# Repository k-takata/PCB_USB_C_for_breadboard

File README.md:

# ブレッドボード用 USB Type-C 電源アダプター (Rev. 4)

## 概要

USB Type-Cからブレッドボードに電源を供給するためのアダプターです。
供給電圧は5Vと3.3Vをジャンパーピンで選択できます。

## 使用したソフトウェア

KiCad 9.0

## 回路図

## 基板パターン図

## 部品表

| Reference           |個数|値    | 説明 |
|---------------------|----|------|------|
|C1                   |   1| 10μF|積層セラミックコンデンサー 3225M|
|D1                   |   1|      |角形LED (あるいは3mm LEDや1608MチップLED)|
|F1 (\*1)             |   1|  1.1A|[ポリヒューズ](https://akizukidenshi.com/catalog/g/g100507/)|
|F2 (\*1)             |   1|  0.5A|[ポリヒューズ](https://akizukidenshi.com/catalog/g/g115300/)、表面実装|
|J1                   |   1|      |[USB Type-Cコネクター](https://akizukidenshi.com/catalog/g/g114356/)|
|J2, J3               |   2|      |細ピンヘッダー 1x2、ブレッドボードへの挿入用、裏面に取り付け|
|J4                   |   1|      |ピンヘッダー 1x3、出力電圧設定用|
|J5                   |   1|      |ピンソケット 1x5|
|R1, R2               |   2|5.1kΩ|1608M|
|R3                   |   1|  1kΩ|1/6Wまたは1/4W、LED電流制限用。値はLEDや好みの明るさに応じて適宜調整 (1kΩ~47kΩ)|
|SW1                  |   1|      |[スライドスイッチ](https://akizukidenshi.com/catalog/g/g115707/)|
|U1 (\*2)             |   1|[LM1117GS-3.3](https://akizukidenshi.com/catalog/g/g116989/)|三端子レギュレーター 3.3V 1A|

注:
* (\*1) F1, F2は使用する電流量や実装後のサイズを考慮してどちらかを選択します。基板上にはF1の表示のみあります。
* (\*2) Rev. 2までは[NJM2845DL1-33](https://akizukidenshi.com/catalog/g/g111299/)でした。

## 作成

以下の順で取り付けるのがお勧めです。

* USBコネクター
* 表面のチップ抵抗: R1, R2, (F2, D1)
* 裏面のチップ部品: U1, C1
* 表面右側の部品: J4, R3, D1
* 裏面のピンヘッダー: J2, J3
* 表面下側のピンソケット: J5
* 表面左側の部品: SW1, F1

J5とSW1は少し干渉するので、J5を少し削る必要があるかもしれません。

## 使用方法

基板裏面に取り付けたピンヘッダーJ2, J3をブレッドボードの電源ラインに挿入して使用します。J2, J3に供給する電圧はJ4にジャンパーピンを挿すことで5Vあるいは3.3Vから選択します。
J2, J3の端子は、USBコネクター側がプラス (シルクには`VDD`あるいは`+`の表示)、反対側がマイナス (シルクには`GND`あるいは`-`の表示)です。向きに注意してください。

SW1が電源スイッチです。電源がオンになっていれば、LEDが点灯します。

5Vと3.3Vの両方を使用したい場合や、D+/D-のデータ線を使用したい場合は、J5にコードを接続して使います。

## 変更差分

### Rev. 3とRev. 4の差分

* 基板の幅を約100mil狭くしました。それに合わせていくつかの部品の位置や向きを変更しています。
* ぐらつきが少なくなるよう、J2,J3のドリル径を0.8mmから0.7mmに変更しています。
* ぐらつきが少なくなるよう、J4のドリル径を0.9mmから0.8mmに変更しています。
* SW1を少し外側にずらしてJ5との干渉を減らしています。

### Rev. 2とRev. 3の差分

* U1を[NJM2845DL1-33](https://akizukidenshi.com/catalog/g/g111299/)から、より安価で薄くて小さい[LM1117GS-3.3](https://akizukidenshi.com/catalog/g/g116989/)に変更しています。これにより、ブレッドボードに挿したときにレギュレーターがブレッドボードに当たらなくなりました。
* D1に角形以外のLEDを取り付けた時に干渉しにくいように、R3の向きを逆に変更しています。
* 基板の厚さの設定を1.2mmに変更しています。

### Rev. 1とRev. 2の差分

* Rev. 1では基板の端ギリギリにシルクを配置していたために、シルクが削れてしまっていました。Rev. 2では基板サイズを少し大きくしてわずかに余裕を持たせてあります。
* Rev. 1ではJ5とSW1が干渉していましたが、Rev. 2ではSW1を少し外側にずらして干渉を減らしています。
* Rev. 2では表面実装のポリヒューズを使えるようにしています。
* Rev. 1では基板の厚さ1.6mmで発注していましたが、Rev. 2では1.2mmで発注しています。(KiCadの設定は1.6mmのまま)

## 完成品

Rev. 1

左から順にRev. 1, Rev. 2, Rev. 3

Rev. 1, Rev. 2, Rev. 3の裏面

左から順にRev. 1, Rev. 2, Rev. 3, Rev. 4

ブレッドボードに挿して使用している例 ([ESP32-C3-WROOM-02 Breakout Board](https://github.com/k-takata/PCB_esp32c3_breakout)とともに)

## License

CC0

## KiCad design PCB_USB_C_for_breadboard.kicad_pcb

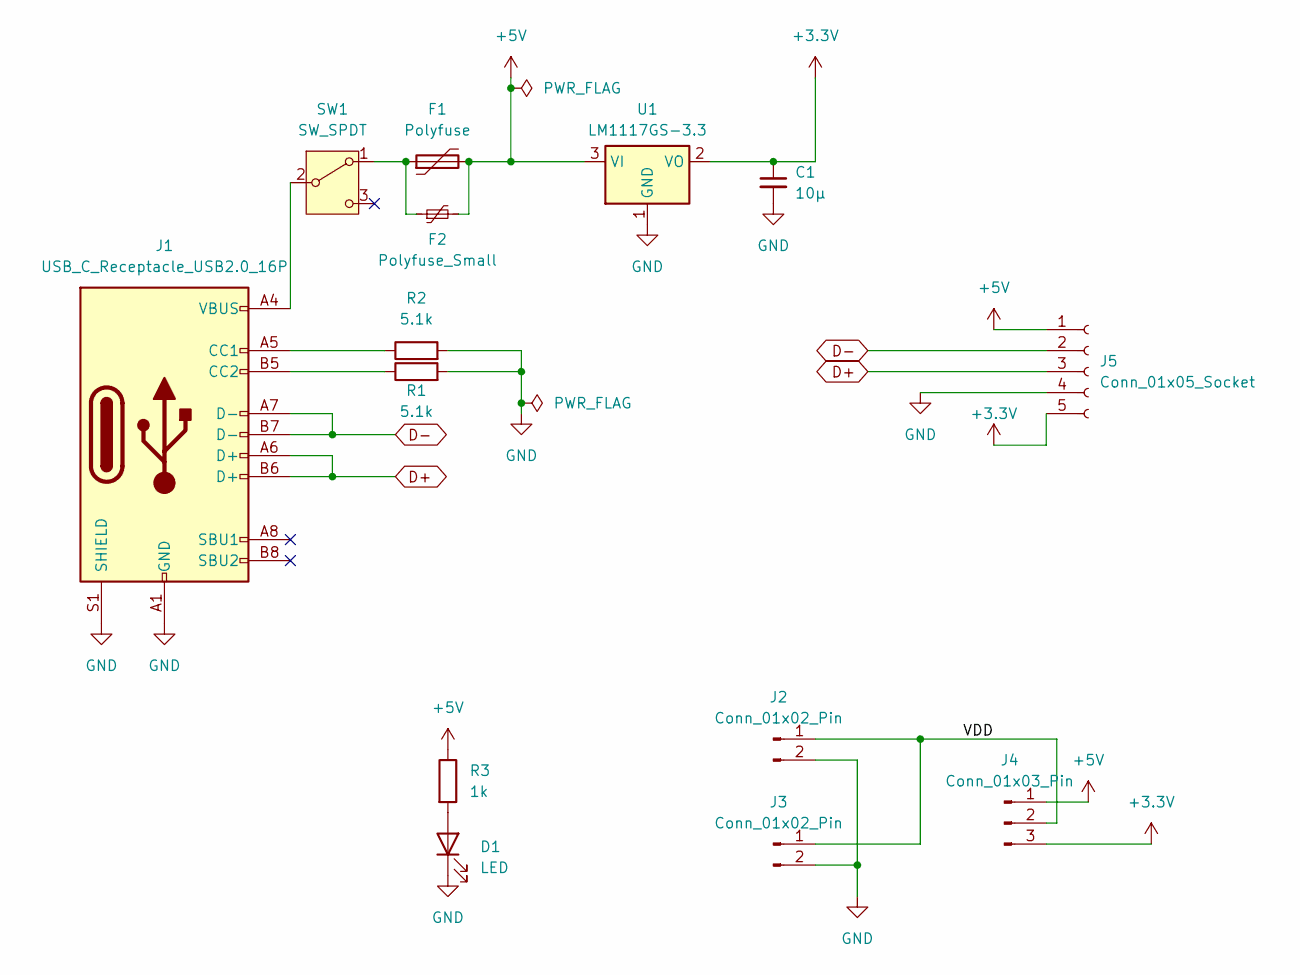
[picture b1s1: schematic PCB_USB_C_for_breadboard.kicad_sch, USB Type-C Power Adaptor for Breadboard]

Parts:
C1: 10μ; C_1210_3225Metric_Pad1.33x2.70mm_HandSolder
D1: LED; LED_Rectangular_W5.0mm_H2.0mm
F1: Polyfuse; C_Disc_D4.3mm_W1.9mm_P5.00mm
F2: Polyfuse_Small; Fuse_1206_3216Metric_Pad1.42x1.75mm_HandSolder
J1: USB_C_Receptacle_USB2.0_16P; USB_C_Receptacle_XKB_U262-16XN-4BVC11
J2, J3: Conn_01x02_Pin; PinHeader_1x02_P2.54mm_Vertical
J4: Conn_01x03_Pin; PinHeader_1x03_P2.54mm_Vertical
J5: Conn_01x05_Socket; PinSocket_1x05_P2.54mm_Vertical
R1, R2: 5.1k; R_0603_1608Metric_Pad0.98x0.95mm_HandSolder
R3: 1k; R_Axial_DIN0204_L3.6mm_D1.6mm_P2.54mm_Vertical
SW1: SW_SPDT; PinHeader_1x03_P2.54mm_Vertical
U1: LM1117GS-3.3; SOT-223-3_TabPin2

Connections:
+3.3V: C1.1, J4.3, J5.5, U1.2 (VO)
+5V: F1.2, F2.2, J4.1, J5.1, R3.1, U1.3 (VI)
/VDD: J2.1, J3.1, J4.2
D+: J1.A6 (D+), J1.B6 (D+), J5.3
D-: J1.A7 (D-), J1.B7 (D-), J5.2
GND: C1.2, D1.1 (K), J1.A1 (GND), J1.A12 (GND), J1.B1 (GND), J1.B12 (GND), J1.S1 (SHIELD), J2.2, J3.2, J5.4, R1.2, R2.2, U1.1 (GND)
unnamed: D1.2 (A), R3.2
unnamed: J1.A5 (CC1), R2.1
unnamed: J1.B5 (CC2), R1.1
unnamed: F1.1, F2.1, SW1.1 (A)
unnamed: J1.A4 (VBUS), J1.A9 (VBUS), J1.B4 (VBUS), J1.B9 (VBUS), SW1.2 (B)

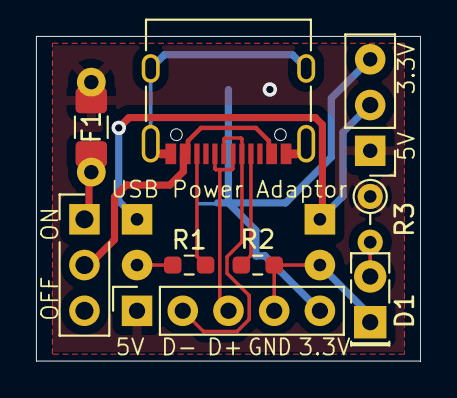
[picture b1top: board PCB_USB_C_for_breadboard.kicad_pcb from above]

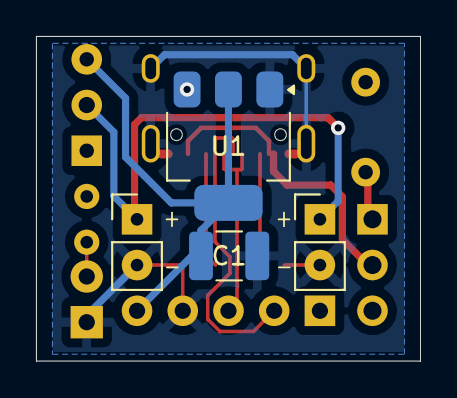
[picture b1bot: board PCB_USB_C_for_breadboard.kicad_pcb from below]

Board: 2 copper layers, 21.3 x 18.0 mm, 14 parts (4 on the bottom side), 11 nets.

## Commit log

2025-06-29 Initial version
2025-06-29 Add title
2025-06-29 Add README
2025-06-30 Update project setting
2025-06-30 Update 3D model
2025-07-10 Update README, add images
2025-07-13 Rev. 2
    * 基板サイズを拡大
    * SW1の位置を調整
    * SMDのポリヒューズを取り付け可能に
2025-07-15 Rev. 3
    * U1をNJM2845DL1-33からLM1117GS-3.3に変更
2025-08-02 微調整
    R3を上下反転。
2025-08-25 Adjust SW1 position
2025-08-31 Adjust hole size
2025-08-31 Set PCB thickness to 1.2mm
2025-08-31 Update README
    Change 1x5 thin pin socket to normal one.
2025-09-11 Rev. 4
    Change the drill sizes.
    * J2, J3: Thin pin header: 0.8mm -> 0.7mm
    * J4: Normal pin header: 0.9mm -> 0.8mm
    J5 keeps 0.9mm to keep margin between SW1.
2025-09-13 Add pictures
2025-10-16 Rev. 4
    Shrink PCB size.
2025-10-24 Update README for Rev. 4
2025-10-30 Revise schema
2025-11-04 Update schema images
2025-11-07 Update PCB pattern image
